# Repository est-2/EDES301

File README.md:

# H1 EDES301
# Repository for EDES301 course work

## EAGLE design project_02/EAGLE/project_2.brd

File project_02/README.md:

# EDES301 Project 02: PCB Design
## Eleanor Tucker
This repository contains EAGLE files and supplementary documentation (bill of materials, Gerber files, etc.) for a PCB based on my Project 01, the Prism Pomodoro. More information about that project can be found in [this repository](linkhttps://github.com/est-2/EDES301/tree/main/project_01).

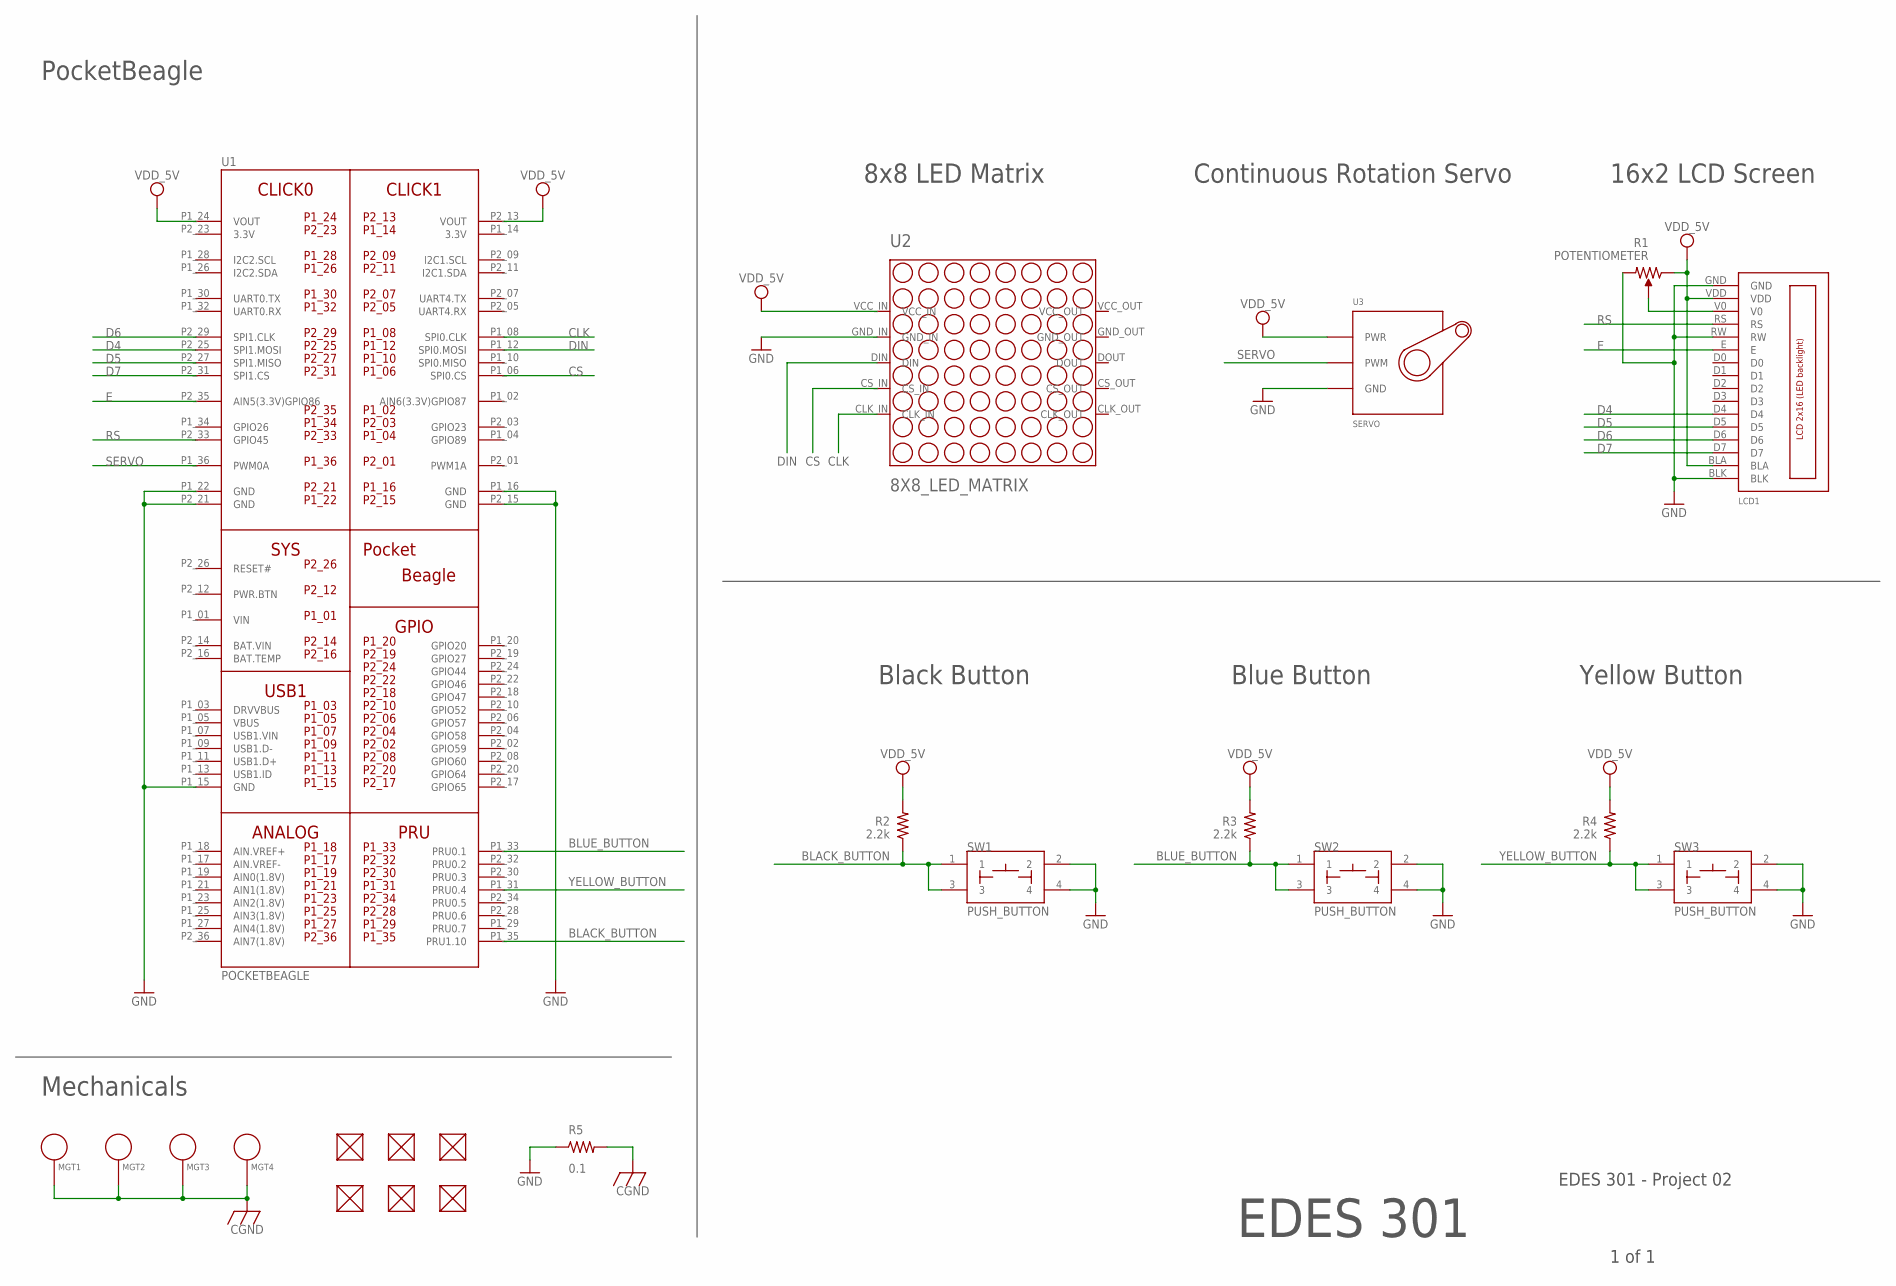
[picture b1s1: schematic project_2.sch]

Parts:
FUD1, FUD2, FUD3, FUD4, FUD5, FUD6: FIDUCIAL; FIDUCIAL_40MIL
LCD1: LCD_2X16_SIL; HY-1602F
MGT1, MGT2, MGT3, MGT4: MOUNTING_HOLE
R1: POTENTIOMETER; POT-PO90S
R2, R3, R4: 2.2k; R0402
R5: 0.1; R0805
SW1, SW2, SW3: PUSH_BUTTON; BUTTON_12.5MM
U1: POCKETBEAGLE
U2: 8X8_LED_MATRIX
U3: SERVO; SERVO-X1

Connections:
3.3V: U1.P1_14 (3.3V), U1.P2_23 (3.3V)
BAT.VIN: U1.P2_14 (BAT.VIN)
BLACK_BUTTON: R2.1, SW1.1, SW1.3, U1.P1_35 (PRU1.10)
BLUE_BUTTON: R3.1, SW2.1, SW2.3, U1.P1_33 (PRU0.1)
CGND: MGT1.P$1, MGT2.P$1, MGT3.P$1, MGT4.P$1, R5.2
CLK: U1.P1_08 (SPI0.CLK), U2.CLK_IN
CS: U1.P1_06 (SPI0.CS), U2.CS_IN
D4: LCD1.D4, U1.P2_25 (SPI1.MOSI)
D5: LCD1.D5, U1.P2_27 (SPI1.MISO)
D6: LCD1.D6, U1.P2_29 (SPI1.CLK)
D7: LCD1.D7, U1.P2_31 (SPI1.CS)
DIN: U1.P1_12 (SPI0.MOSI), U2.DIN
E: LCD1.E, U1.P2_35 (AIN5(3.3V)GPIO86)
GND: LCD1.BLK, LCD1.GND, LCD1.RW, R1.CW, R5.1, SW1.2, SW1.4, SW2.2, SW2.4, SW3.2, SW3.4, U1.P1_15 (GND), U1.P1_16 (GND), U1.P1_22 (GND), U1.P2_15 (GND), U1.P2_21 (GND), U2.GND_IN, U3.GND
RS: LCD1.RS, U1.P2_33 (GPIO45)
SERVO: U1.P1_36 (PWM0A), U3.SIG (PWM)
V0: LCD1.V0, R1.S
VDD_5V: LCD1.BLA, LCD1.VDD, R1.CCW, R2.2, R3.2, R4.2, U1.P1_24 (VOUT), U1.P2_13 (VOUT), U2.VCC_IN, U3.PWR
VIN: U1.P1_01 (VIN)
YELLOW_BUTTON: R4.1, SW3.1, SW3.3, U1.P1_31 (PRU0.4)

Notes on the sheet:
EDES 301 - Project 02
Mechanicals
PocketBeagle
8x8 LED Matrix
Continuous Rotation Servo
16x2 LCD Screen
Black Button
Blue Button
Yellow Button
1 of 1
EDES 301

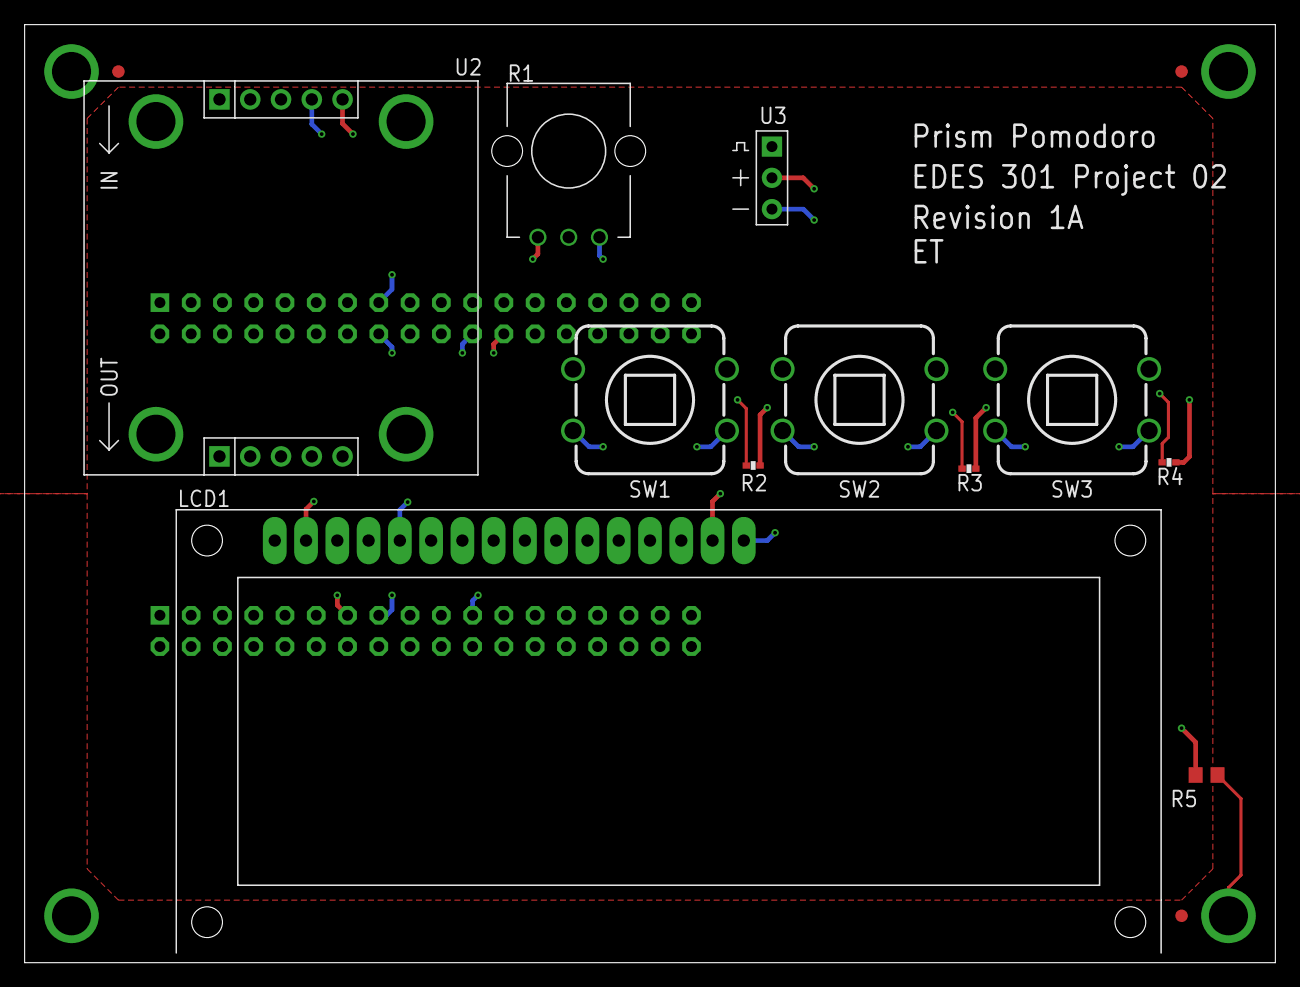
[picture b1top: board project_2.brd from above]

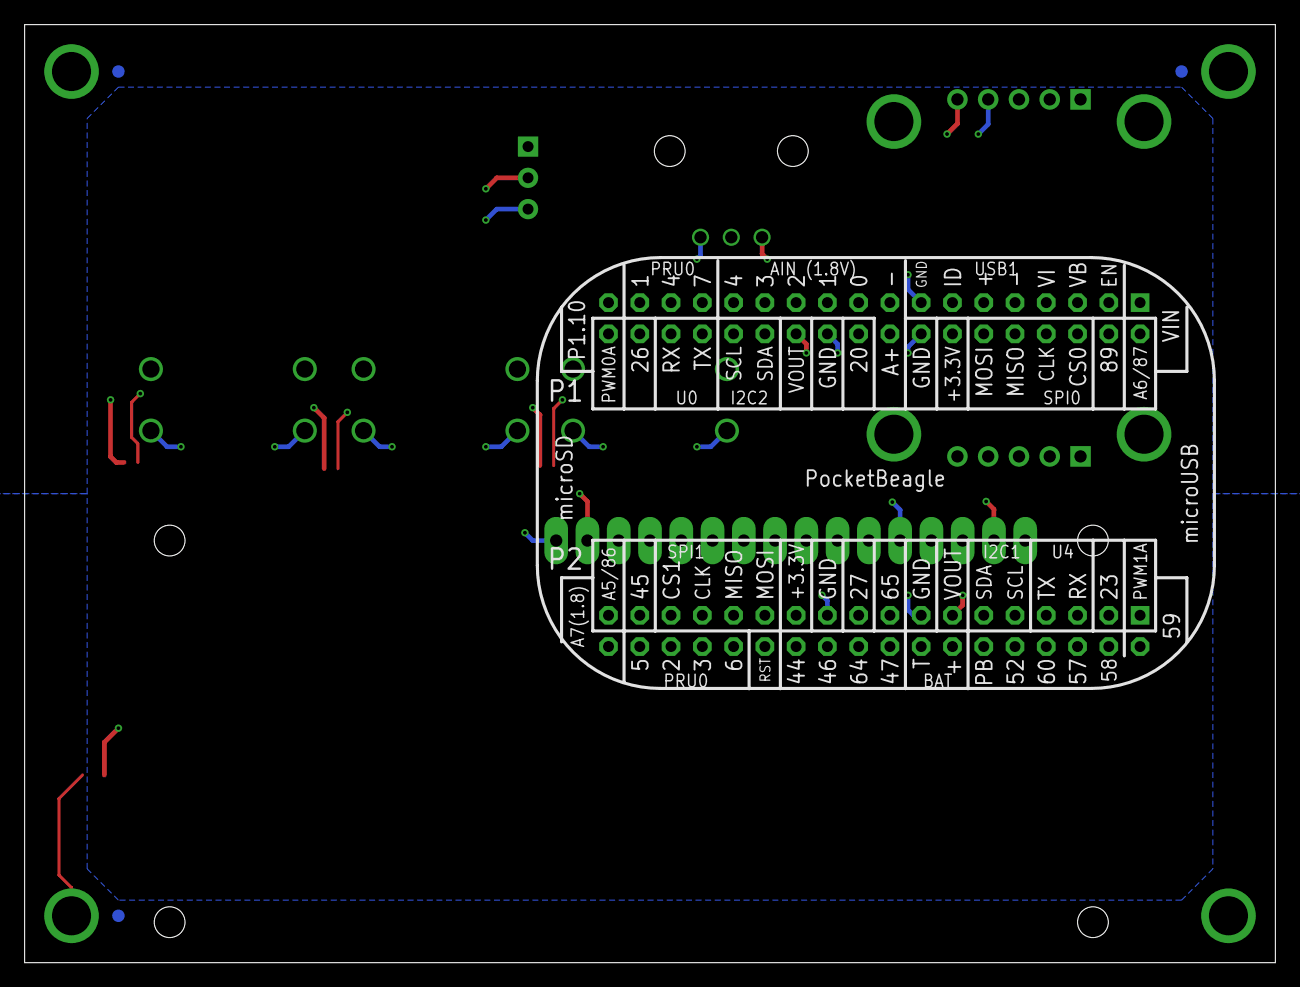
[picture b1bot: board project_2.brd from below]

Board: 4 copper layers, 101.6 x 76.2 mm, 22 parts (4 on the bottom side), 18 nets.

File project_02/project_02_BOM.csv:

Qty,Value,Device,Package,Designator(s),Description,Manufacturer / MPN
1,0.1,R_R0805,R0805,R5,Resistor,
3,2.2k,R_R0402,R0402,"R2, R3, R4",Resistor,
1,8X8_LED_MATRIX,8X8_LED_MATRIX,8X8_LED_MATRIX,U2,"Small 1.2"" 8x8 Ultra Bright Red LED Matrix - KWM-30881CVB",Adafruit 455
6,FIDUCIAL,FIDUCIAL,FIDUCIAL_40MIL,"FUD1, FUD2, FUD3, FUD4, FUD5, FUD6",Fiducials for aiding in manufacture,
1,LCD_2X16_SIL,LCD_2X16_SIL,HY-1602F,LCD1,Standard LCD 16x2 - white on blue,Adafruit 181
4,MOUNTING_HOLE,MOUNTING_HOLE,MOUNTING_HOLE,"MGT1, MGT2, MGT3, MGT4",Chassis mounting hole with GND connection ability,
1,POCKETBEAGLE,POCKETBEAGLE,POCKETBEAGLE,U1,PocketBeagle development board,BeagleBoard
1,POTENTIOMETER,POTENTIOMETER,POT-PO90S,R1,Potentiometer,
3,PUSH_BUTTON,PUSH_BUTTON,BUTTON_12.5MM,"SW1, SW2, SW3",Round tactile button switch,Adafruit 1009
1,SERVO,SERVO,SERVO-X1,U3,Continuous Rotation Servo - FeeTech FS5103R,Adafruit 154

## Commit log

2025-02-05 Updating README.md
2025-02-18 Added four operators
2025-02-18 added compatibility with Python 2
2025-02-18 cleaned up
2025-02-19 fixed issue
2025-02-24 Added project_01
2025-03-01 added 7-segment display and level shifter
2025-03-08 added software diagram and python classes
2025-04-23 added spi pins
2025-04-23 specified spi pin functions
2025-04-24 LED matrix hardware driver
2025-04-24 updated pin configuration
2025-04-24 updated test
2025-04-24 more files
2025-04-24 backup
2025-04-24 stored matrix initialization
2025-04-24 updated LCD driver
2025-04-25 added set study time feature
2025-04-26 removed P1_08 due to error
2025-04-26 added write_two_lines function
2025-04-26 added invalid time error
2025-04-26 added study mode
2025-04-27 added servo
2025-04-27 added run function
2025-04-27 refined run function
2025-05-02 updated documentation
2025-05-02 added special case for break_time = 1
2025-05-02 udpate
2025-05-03 fixed readme formatting
2025-05-03 deleted old files
2025-05-03 added servo calibration code
2025-05-03 formatting
2025-05-04 added delay in _setup
2025-05-04 updated readme formatting
2025-05-04 added Hackster.io link
2025-05-06 added ppt and EAGLE files
2025-05-06 organized files
2025-05-07 added BOM
2025-05-07 added Gerber files
2025-05-07 added schematic
